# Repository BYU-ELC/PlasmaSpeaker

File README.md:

# PlasmaSpeaker
Flyback Plasma Speaker Demo

See [Wiki](https://github.com/BYU-ELC/PlasmaSpeaker/wiki) for project documentation

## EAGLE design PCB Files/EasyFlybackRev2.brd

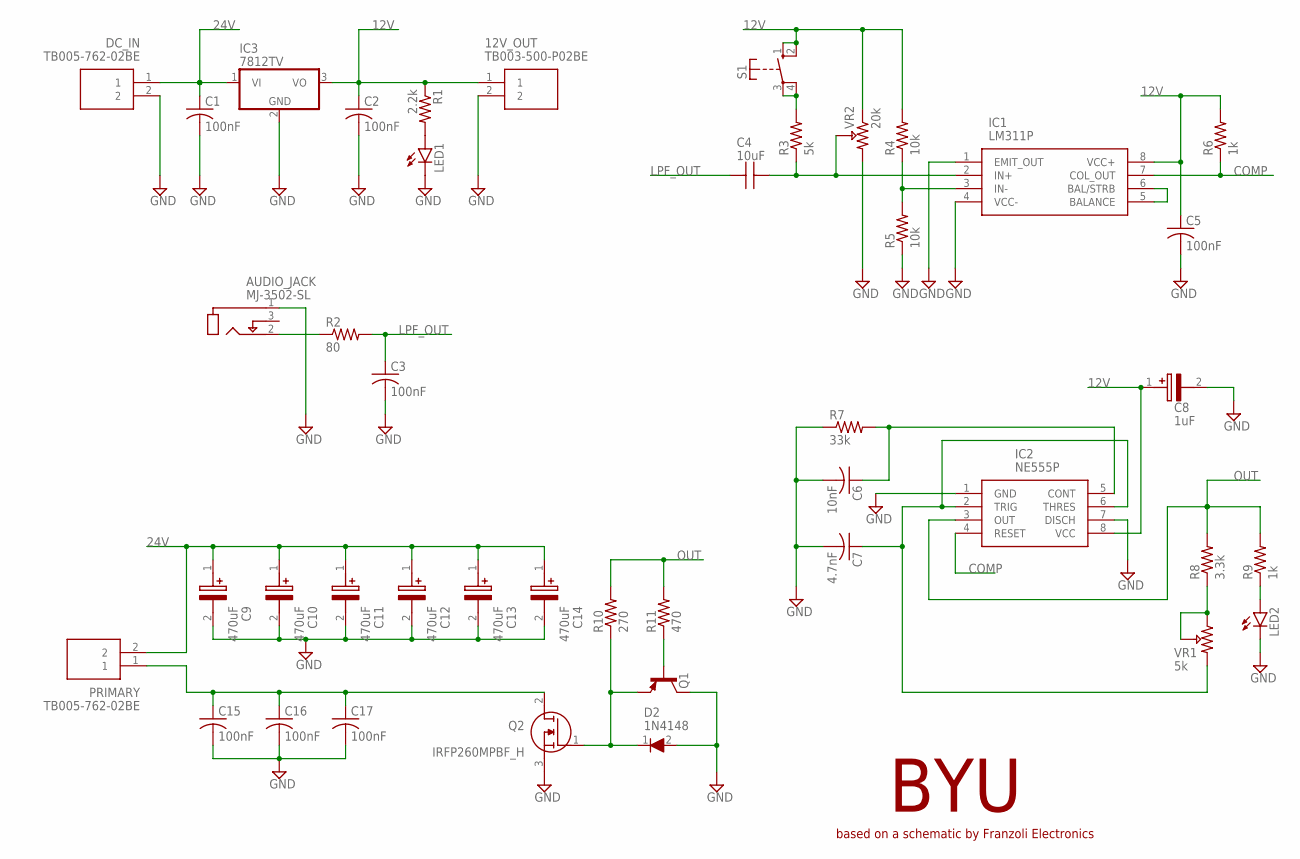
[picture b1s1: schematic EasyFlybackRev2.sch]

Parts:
12V_OUT: TB003-500-P02BE; SHDR2W100P0X500_1X2_1000X780X1
AUDIO_JACK: MJ-3502-SL; MJ3502-SL
C1, C2, C3, C5: 100nF; C025-024X044
C4: 10uF; RCE7U2J103J3K1H03B
C6: 10nF; C025-024X044
C7: 4.7nF; C025-024X044
C8: 1uF; TAP105K035SCS
C9, C10, C11, C12, C13, C14: 470uF; CAPPRD500W65D1000H1700
C15, C16, C17: 100nF; MKP1G031004D00KSSD
D2: 1N4148; DIOAD1068W53L380D172
DC_IN: TB005-762-02BE; TB00576202BE
IC1: LM311P; DIP794W53P254L959H508Q8N
IC2: NE555P; DIP794W53P254L959H508Q8N
IC3: 7812TV; TO220V
LED1, LED2: LED5MM
PRIMARY: TB005-762-02BE; TB00576202BE
Q1: -PNP-TO92-E1; TO92-E1
Q2: IRFP260MPBF_H; TO545P520X1594X2550-3P_H
R1: 2.2k; 0207/10
R2: 80; 0207/10
R3: 5k; 0207/10
R4, R5: 10k; 0207/10
R6, R9: 1k; 0207/10
R7: 33k; 0207/10
R8: 3.3k; 0207/10
R10: 270; 0207/10
R11: 470; 0207/10
S1: DTE6K
VR1: 5k; PV36W502C01B00
VR2: 20k; PV36W502C01B00

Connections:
12V: 12V_OUT.1, C2.1, C5.1, C8.1 (+), IC1.8 (VCC+), IC2.8 (VCC), IC3.3 (VO), R1.1, R4.2, R6.2, S1.1 (S), S1.2 (S), VR2.1 (CCW)
24V: C1.1, C9.1 (+), C10.1 (+), C11.1 (+), C12.1 (+), C13.1 (+), C14.1 (+), DC_IN.1, IC3.1 (VI), PRIMARY.2
COMP: IC1.7 (COL_OUT), IC2.4 (RESET), R6.1
GND: 12V_OUT.2, AUDIO_JACK.1, C1.2, C2.2, C3.2, C5.2, C6.2, C7.2, C8.2 (-), C9.2 (-), C10.2 (-), C11.2 (-), C12.2 (-), C13.2 (-), C14.2 (-), C15.P$2 (2), C16.P$2 (2), C17.P$2 (2), D2.2 (A), DC_IN.2, IC1.1 (EMIT_OUT), IC1.4 (VCC-), IC2.1 (GND), IC2.7 (DISCH), IC3.2 (GND), LED1.K (C), LED2.K (C), Q1.1 (C), Q2.3 (S), R5.1, R7.1, VR2.3 (CW)
LPF_OUT: C3.1, C4.1, R2.2
unnamed: C15.P$1 (1), C16.P$1 (1), C17.P$1 (1), PRIMARY.1, Q2.2 (D)
unnamed: LED1.A, R1.2
unnamed: AUDIO_JACK.2, R2.1
unnamed: D2.1 (K), Q1.3 (E), Q2.1 (G), R10.1
unnamed: R3.2, S1.3, S1.4
unnamed: IC1.5 (BALANCE), IC1.6 (BAL/STRB)
unnamed: Q1.2 (B), R11.1
unnamed: C7.1, IC2.2 (TRIG), IC2.6 (THRES), VR1.3 (CW)
unnamed: R8.1, VR1.1 (CCW), VR1.2 (WIPER)
unnamed: C6.1, IC2.5 (CONT), R7.2
unnamed: LED2.A, R9.1
unnamed: IC1.3 (IN-), R4.1, R5.2
unnamed: C4.2, IC1.2 (IN+), R3.1, VR2.2 (WIPER)
OUT: IC2.3 (OUT), R8.2, R9.2, R10.2, R11.2

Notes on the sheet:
BYU
based on a schematic by Franzoli Electronics

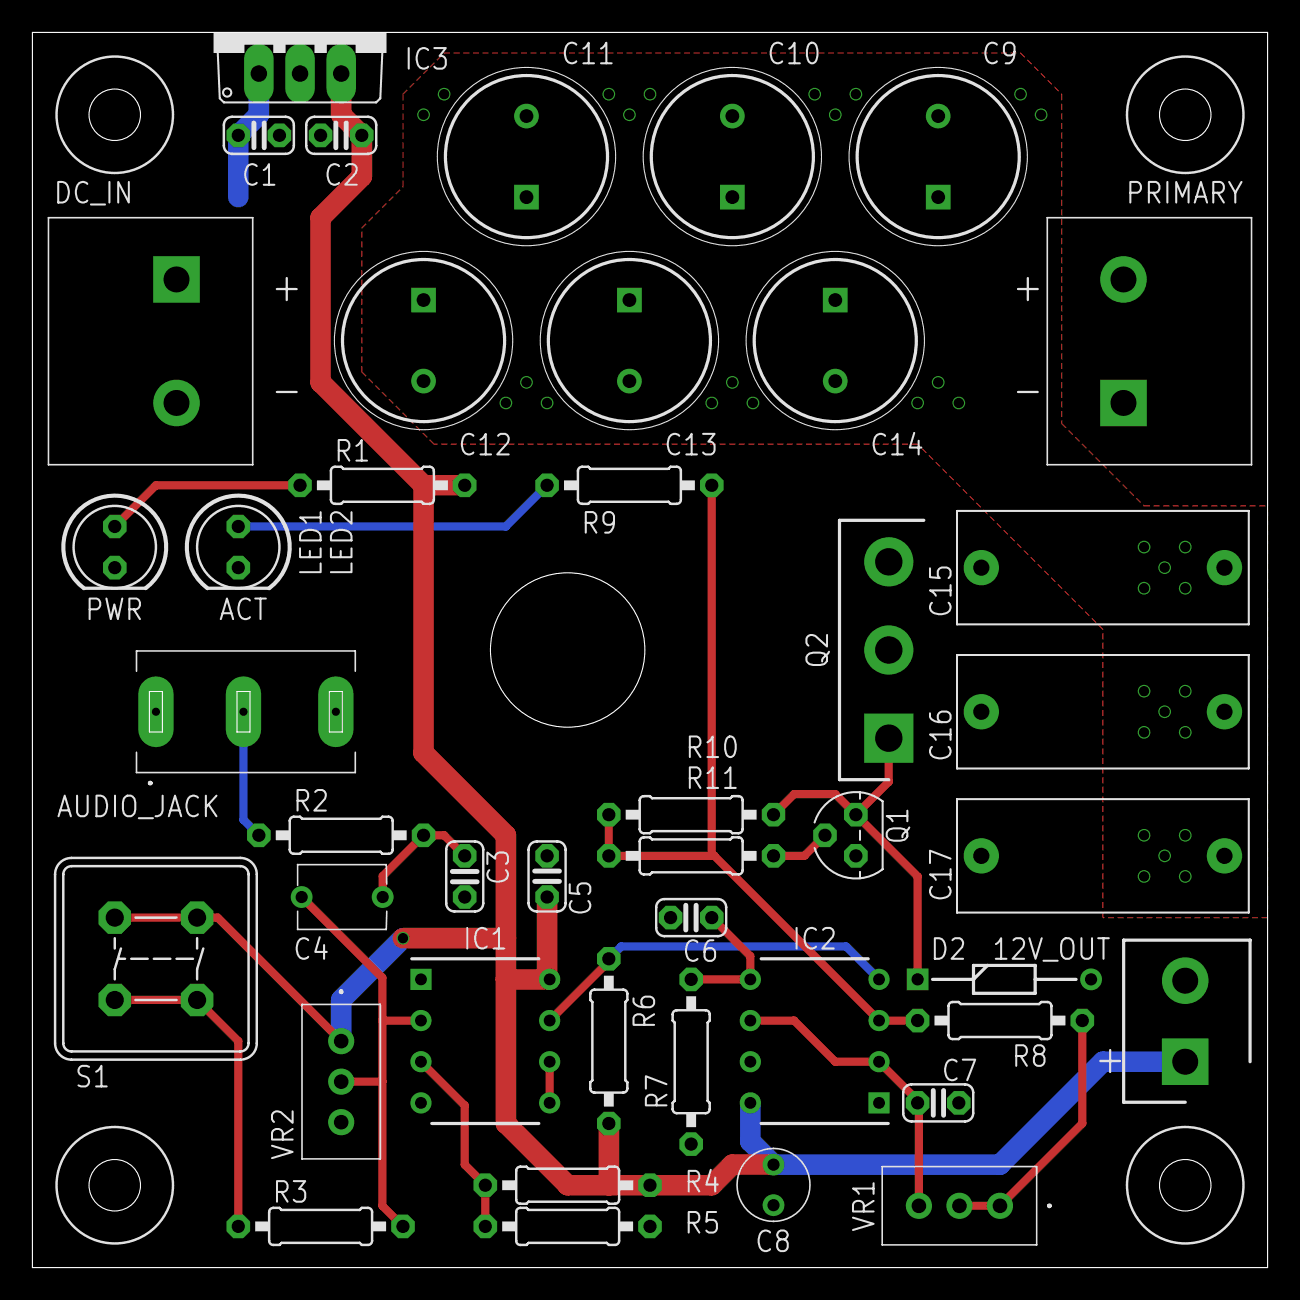
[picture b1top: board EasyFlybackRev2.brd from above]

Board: 2 copper layers, 76.2 x 76.2 mm, 43 parts (0 on the bottom side), 19 nets.

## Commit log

2022-06-23 Add wiki link to README
2022-06-25 Update wiki link to BYU-ELC owner
